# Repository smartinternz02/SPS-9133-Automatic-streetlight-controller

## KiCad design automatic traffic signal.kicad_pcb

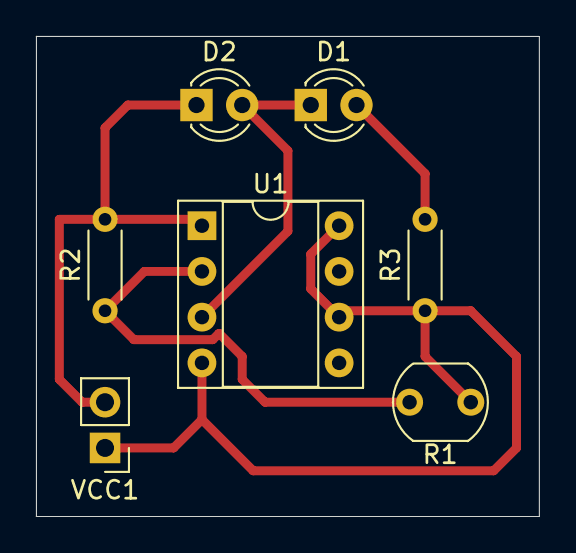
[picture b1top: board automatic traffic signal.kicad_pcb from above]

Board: 2 copper layers, 27.9 x 26.7 mm, 7 parts (0 on the bottom side), 5 nets.

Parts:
D1: RED LED; LED_D3.0mm
D2: GREEN LED; LED_D3.0mm
R1: LDR07; R_LDR_5.1x4.3mm_P3.4mm_Vertical
R2: 47K; R_Axial_DIN0204_L3.6mm_D1.6mm_P5.08mm_Horizontal
R3: 330E; R_Axial_DIN0204_L3.6mm_D1.6mm_P5.08mm_Horizontal
U1: LM555; DIP-8_W7.62mm_Socket
VCC1: DC 9; PinHeader_1x02_P2.54mm_Vertical

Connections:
unnamed: D1.1, D2.2, U1.3
unnamed: D1.2, R3.2
unnamed: D2.1, R2.2, U1.1, VCC1.2
unnamed: R1.1, R3.1, U1.4, U1.6, U1.8, VCC1.1
unnamed: R1.2, R2.1, U1.2

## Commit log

2021-03-24 Create Final Video LINK
